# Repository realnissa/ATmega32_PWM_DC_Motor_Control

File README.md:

# ATmega32 PWM DC Motor Control

A PWM-based DC motor speed control system built with the ATmega32 microcontroller. The system uses Timer0 (OC0/PB3) to generate a PWM signal that drives a DC motor through an N-channel MOSFET, with push-button speed control and LED speed-level indicators.

## Project Overview

This project demonstrates pulse-width modulation (PWM) as a method of controlling the average power delivered to a DC motor. Instead of simply switching the motor ON/OFF, the ATmega32 generates a variable-duty-cycle square wave that adjusts motor speed smoothly across five discrete levels (0%, 25%, 50%, 75%, 100%).

| Control | Function |
|---|---|
| Increase button (PA0) | Raises PWM duty cycle by one level |
| Decrease button (PA1) | Lowers PWM duty cycle by one level |
| Stop button (PA2) | Immediately sets duty cycle to 0% |
| LEDs (PB0–PB2) | Indicate current speed level |
| PWM output (PB3 / OC0) | Drives the motor via MOSFET switching |

## System Block Diagram

```
[Push Buttons] --> [ATmega32: Timer0 PWM] --> [Gate Resistor] --> [MOSFET] --> [DC Motor]
                            |                                          |
                       [LED Indicators]                          [Flyback Diode]
```

## Hardware Summary

| Component | Designator | Purpose |
|---|---|---|
| ATmega32-P | U1 | Main controller and PWM generator |
| DC Motor | M1 | Controlled actuator |
| N-Channel MOSFET | Q1 | Motor driver (low-side switch) |
| 1N4007 Diode | D4 | Flyback / back-EMF protection |
| Push buttons | SW1–SW4 | Increase, decrease, stop, reset |
| LEDs | D1–D3 | Speed-level indication |
| 8 MHz Crystal | Y1 | External clock source |
| 220 ohm resistor | R2 | MOSFET gate current limiting |
| 330 ohm resistors | R3–R5 | LED current limiting |
| 10 kohm resistor | R1 | Reset pull-up |

Full pin assignments are documented in [`documentation/pin_mapping_table.md`](documentation/pin_mapping_table.md).

## How PWM Speed Control Works

The ATmega32's Timer0 is configured in Fast PWM mode, outputting on PB3 (OC0). The duty cycle is controlled by the OCR0 register:

```
D ≈ (OCR0 / 255) x 100%
```

Pressing the increase or decrease button changes OCR0 in steps, moving the motor between five predefined speed levels. Full calculations are in [`documentation/duty_cycle_calculation.md`](documentation/duty_cycle_calculation.md), and the timer/register configuration is explained in [`documentation/pwm_configuration.md`](documentation/pwm_configuration.md).

## Repository Structure

```
ATmega32_PWM_DC_Motor_Control/
│
├── README.md
│
├── firmware/
│   ├── src/            # Firmware source code (.c)
│   ├── include/        # Header files (.h)
│   └── hex/            # Compiled .hex output
│
├── kicad/
│   ├── schematic/      # KiCad schematic files
│   ├── pcb/            # KiCad PCB layout files
│   └── gerber/         # Generated Gerber fabrication files
│
├── simulide/
│   ├── circuit/        # SimulIDE circuit file (.sim1)
│   └── screenshots/    # Simulation screenshots
│
├── documentation/
│   ├── block_diagram.png
│   ├── flowchart.png
│   ├── pwm_configuration.md
│   ├── duty_cycle_calculation.md
│   ├── pin_mapping_table.md
│   └── test_results.md
│
└── media/
    └── demonstration_video_link.txt
```

## Tools Used

| Tool | Purpose |
|---|---|
| KiCad | Schematic design and PCB layout |
| MPLAB for VS Code | Firmware development (C) |
| SimulIDE | Circuit simulation and PWM verification |
| Git / GitHub | Version control and submission |

## Firmware Behavior

```
main()
{
    initialize_gpio();
    initialize_pwm();
    while(1)
    {
        read_buttons();
        update_duty_cycle();
        update_speed_indicators();
    }
}
```

Source code is available in [`firmware/src/`](firmware/src/), and the compiled `.hex` file used for both hardware programming and SimulIDE simulation is in [`firmware/hex/`](firmware/hex/).

## Simulation

The circuit was simulated in SimulIDE before PCB fabrication to verify PWM generation, button response, LED indication, and motor behavior. An oscilloscope probe on PB3 confirmed the PWM waveform changed correctly across all five speed levels. Full results are documented in [`documentation/test_results.md`](documentation/test_results.md).

## Status

| Stage | Status |
|---|---|
| Schematic design (KiCad) | Complete |
| PCB layout (KiCad) | Complete |
| DRC / ERC checks | Complete |
| Firmware (PWM, buttons, LEDs) | Complete |
| SimulIDE simulation | Complete |
| Gerber file generation | Complete |
| Documentation | Complete |

## Extension (Optional)

A suggested next step for this project is closed-loop speed control using a rotary encoder, where the ATmega32 measures actual motor speed from encoder pulses and adjusts the PWM duty cycle automatically to maintain a target speed.

## Author

Student project for ATmega32 PWM-based DC Motor Speed Control assignment.

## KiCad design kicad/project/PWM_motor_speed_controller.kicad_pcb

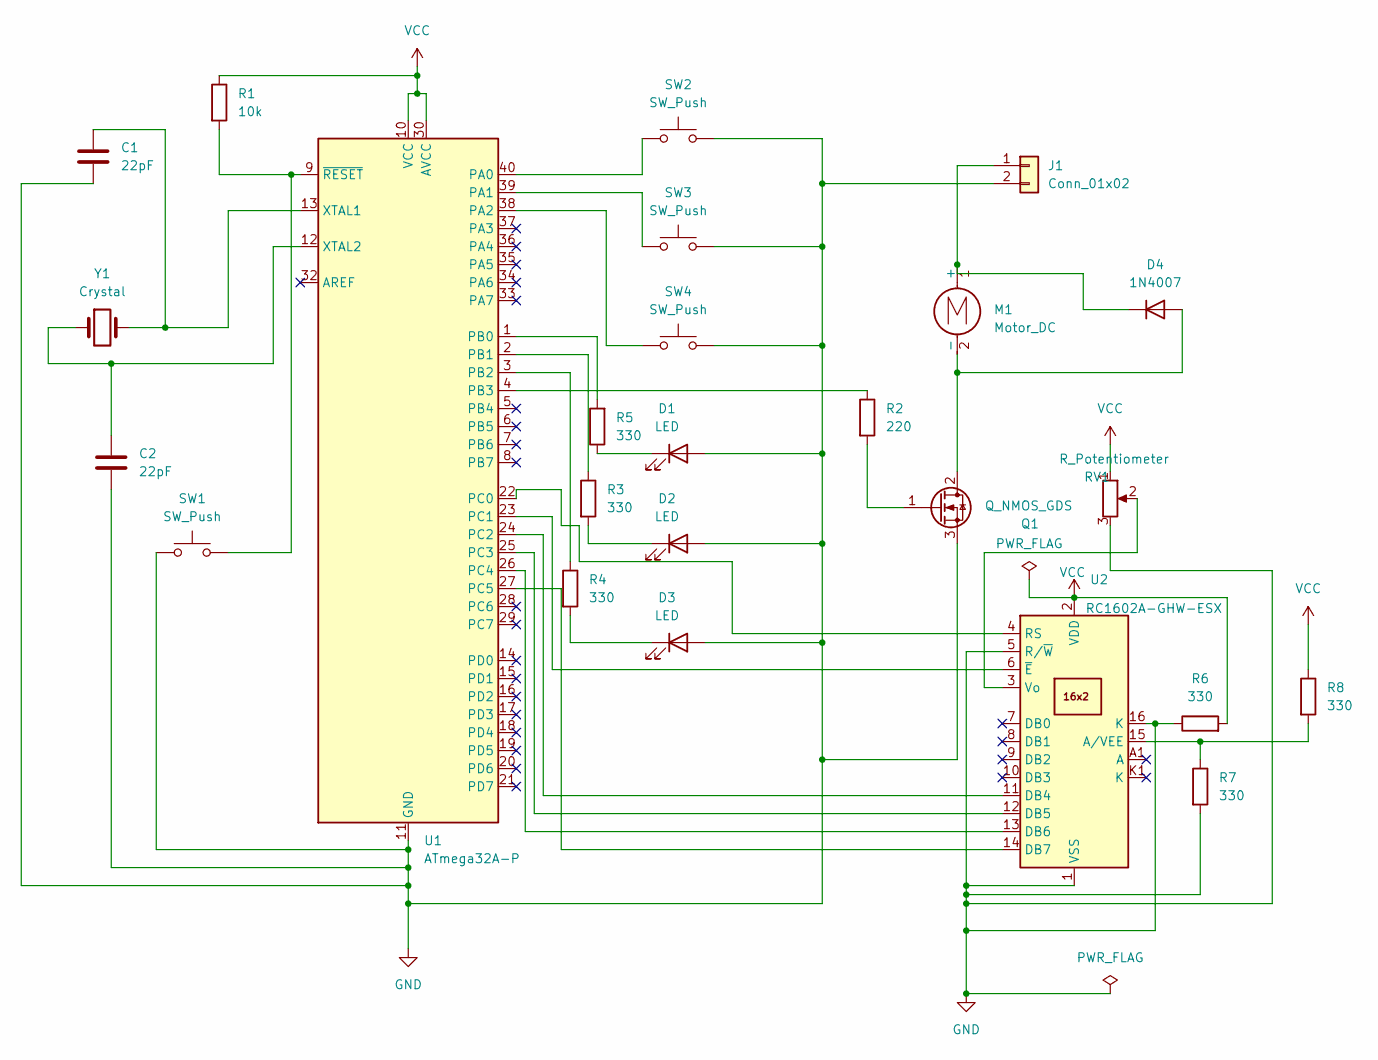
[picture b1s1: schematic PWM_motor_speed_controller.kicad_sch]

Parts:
C1, C2: 22pF; C_Disc_D3.0mm_W1.6mm_P2.50mm
D1, D2, D3: LED; LED_D5.0mm
D4: 1N4007; D_DO-41_SOD81_P10.16mm_Horizontal
J1: Conn_01x02; PinHeader_1x02_P2.54mm_Vertical
M1: Motor_DC; PinHeader_1x02_P2.54mm_Vertical
Q1: Q_NMOS_GDS; TO-92_Inline
R1: 10k; R_Axial_DIN0204_L3.6mm_D1.6mm_P7.62mm_Horizontal
R2: 220; R_Axial_DIN0204_L3.6mm_D1.6mm_P7.62mm_Horizontal
R3, R4, R5, R6, R7, R8: 330; R_Axial_DIN0204_L3.6mm_D1.6mm_P7.62mm_Horizontal
RV1: R_Potentiometer; Potentiometer_Bourns_3386P_Vertical
SW1, SW2, SW3, SW4: SW_Push; SW_PUSH_6mm
U1: ATmega32A-P; DIP-40_W15.24mm
U2: RC1602A-GHW-ESX; RC1602A
Y1: Crystal; Crystal_HC49-U_Vertical

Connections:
GND: C1.2, C2.2, D1.2 (A), D2.2 (A), D3.2 (A), J1.2, Q1.3 (S), R6.1, R7.2, RV1.3, SW1.1, SW2.2, SW3.2, SW4.2, U1.11 (GND), U1.31 (GND), U2.1 (VSS), U2.5 (R/~W), U2.16 (K)
unnamed: D1.1 (K), R5.1
unnamed: D2.1 (K), R3.2
unnamed: D3.1 (K), R4.2
unnamed: D4.2 (A), M1.2 (-), Q1.2 (D)
unnamed: D4.1 (K), J1.1, M1.1 (+)
unnamed: Q1.1 (G), R2.2
unnamed: SW2.1, U1.40 (PA0)
unnamed: SW3.1, U1.39 (PA1)
unnamed: SW4.1, U1.38 (PA2)
unnamed: R5.2, U1.1 (PB0)
unnamed: R3.1, U1.2 (PB1)
unnamed: R4.1, U1.3 (PB2)
unnamed: R2.1, U1.4 (PB3)
unnamed: U1.22 (PC0), U2.4 (RS)
unnamed: U1.23 (PC1), U2.6 (~E)
unnamed: U1.24 (PC2), U2.11 (DB4)
unnamed: U1.25 (PC3), U2.12 (DB5)
unnamed: U1.26 (PC4), U2.13 (DB6)
unnamed: U1.27 (PC5), U2.14 (DB7)
unnamed: C1.1, U1.13 (XTAL1), Y1.2
unnamed: C2.1, U1.12 (XTAL2), Y1.1
unnamed: R1.2, SW1.2, U1.9 (~RESET)
unnamed: R7.1, R8.2, U2.15 (A/VEE)
unnamed: RV1.2, U2.3 (Vo)
VCC: R1.1, R6.2, R8.1, RV1.1, U1.10 (VCC), U1.30 (AVCC), U2.2 (VDD)

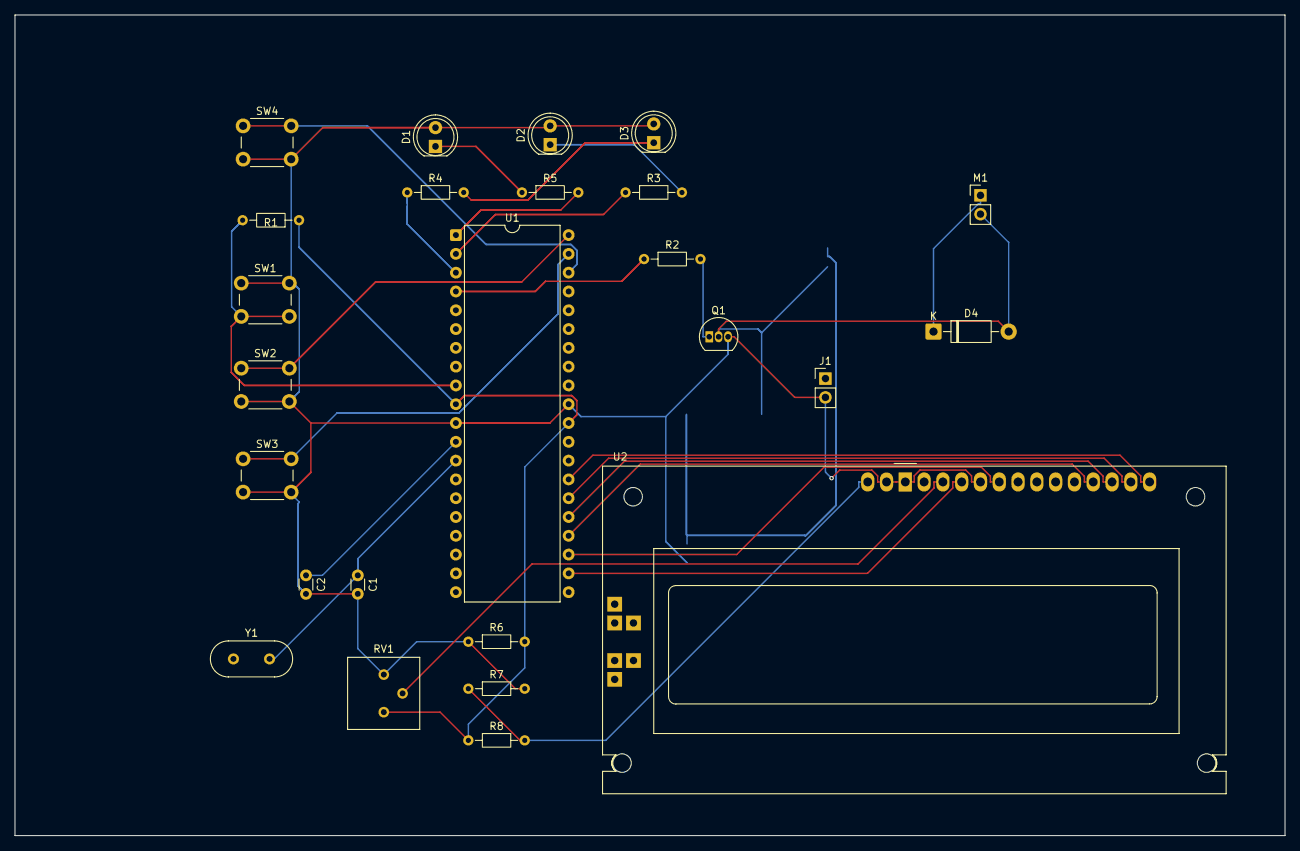
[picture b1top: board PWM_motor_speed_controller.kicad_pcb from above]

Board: 2 copper layers, 171.7 x 110.9 mm, 25 parts (0 on the bottom side), 26 nets.

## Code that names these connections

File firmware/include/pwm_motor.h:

#ifndef PWM_MOTOR_H
#define PWM_MOTOR_H

#include <avr/io.h>
#include <avr/interrupt.h>
#include <util/delay.h>
#include <stdint.h>

#define F_CPU           8000000UL

// Pini za LCD kwenye PORTC
#define LCD_DDR         DDRC
#define LCD_PORT        PORTC
#define RS_PIN          PC0
#define EN_PIN          PC1

#define PWM_DDR         DDRB
#define PWM_PORT        PORTB
#define PWM_PIN         PB3

#define BTN_DDR         DDRA
#define BTN_PORT        PORTA
#define BTN_PIN         PINA

#define BTN_INC_PIN     PA0
#define BTN_DEC_PIN     PA1
#define BTN_STOP_PIN    PA2

#define LED_DDR         DDRB
#define LED_PORT        PORTB

#define LED_LOW_PIN     PB0
#define LED_MED_PIN     PB1
#define LED_HIGH_PIN    PB2

#define SPEED_LEVELS        5
#define SPEED_MIN           0
#define SPEED_MAX           4

#define OCR0_LEVEL_0        0
#define OCR0_LEVEL_1        64
#define OCR0_LEVEL_2        128
#define OCR0_LEVEL_3        191
#define OCR0_LEVEL_4        255

#define DEBOUNCE_DELAY_MS   20

void initialize_gpio(void);
void initialize_pwm(void);
void set_pwm_duty_cycle(uint8_t level);
void read_buttons(void);
void update_duty_cycle(void);
void update_speed_indicators(void);
uint8_t debounce_button(uint8_t pin_mask);

// === Kazi za LCD ===
void lcd_command(uint8_t cmd);
void lcd_char(uint8_t data);
void lcd_init(void);
void lcd_string(const char *str);
void lcd_set_cursor(uint8_t row, uint8_t col);
void update_lcd_display(void);

#endif

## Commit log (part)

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2026-06-17 Added project files
